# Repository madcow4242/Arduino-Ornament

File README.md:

# Arduino-powered Christmas Ornament (or badge, or anything else)

A custom LED Christmas ornament with advent calendar functionality, built using Arduino and KiCad.  This project can easily be adapted to other formats such as a badge by changing the PCB layout.  

### Key features:
- 30 individually-addressable LEDs
- PWM LED control, with support for up to 12 (or more) simultaneous LEDs
- Fade-in / Fade-out support
- Advent calendar mode included
- User-configurable advent date and brightness settings
- Light level measurement (optional)
- Current measurement via a precision 1-ohm current sense resistor and precision amplified ADC circuit (intended to help optimize power usage prior to software finalization) (optional)
- Optimized to fit within the 4k / 256 byte memory limitations of the ATTiny414, but is also compatible with larger variants such as the ATTiny 814/1614/824/1624/3224
- Production software is configured to run at 8MHz to optimize power usage (instead of default 20MHz) - this can be changed if higher PWM frequency is desired, for example.  (test software still runs at 20MHz)
- \>30 days run time on one set of 3x AAA batteries, using default Production software (5 hours/day on, with auto timer).  Can be run on other 3-5VDC power sources like CR2032 for shorter durations (however, \>3.5V is required for 2.8V LEDs or higher - so stick with ~2.2V LEDs or lower if using 3-3.3V power sources).

## Project Structure

This project is organized into three main directories:

### 1. KiCad Files (`KiCad_PCB_Ornament/`)
Contains all KiCad design files for the PCB:
- Schematic files (.kicad_sch)
- PCB layout files (.kicad_pcb)
- Component libraries (.lib, .dcm)
- Footprint files (.kicad_mod)
- Exported fabrication files (.gbr, .drl) (for the example design / messaging)

The PCB layout can be easily customized with your own text, or into a different physical format or size (like a badge) using KiCad - however if modifying the layout you'll have to re-route the board as well of course.  I chose to put the control electronics on the front of the board (to be geeky), but they could easily be moved to the back to clean up the appearance.

NOTE: the board design includes optional current monitoring circuit and light sensing circuit.  Neither of these are implemented in the production software, however they are fully functional and usable in the test software.  Those features can be ported to production as needed, or removed or unpopulated on the PCB.

### 2. Production Software (`Ornament_production_1/`)
The main firmware for the ornament controller:
- Main Arduino sketch (`Ornament_production_1.ino`)
- Configuration and constants
- LED control algorithms
- Date setting and brightness adjustment routines
- Software fits in under 4k of flash, and uses approx. 70 (of 256) bytes of dynamic storage

### 3. Test/Validation Software (`Ornament_test_1/`)
Code for testing and validating the PCB functionality:
- Calibration routines
- Basic functionality tests
- Hardware verification code
- Software uses less than the ATTiny414's 4k of flash and 256 bytes of dynamic storage
- Includes ADC routines for current monitoring and light level measurement, if needed (not used in production code)

## Production Features

- Advent calendar display (December 1-25)
- Custom LED patterns with twinkling effects, including PWM fade-in, fade-out
- Date setting via button interface
- Adjustable brightness levels (10% to 100%)
- Sleep/wake cycle automation
- Preview mode for manual activation during sleep, without affecting 24-hour auto-on timer

## Hardware Requirements

- Microchip ATtiny414 microcontroller (or others in that series)
- Custom PCB with LED matrix
- Power switch and button for user interface
- Battery or power supply for operation
- Optional serial monitor to view diagnostic output on the UART connections (test software only by default)

## Getting Started

1. Clone this repository
2. Open the KiCad project to view or modify the PCB design
3. Use the Arduino IDE to compile and upload the production firmware to the completed PCB
4. Test with the validation software to verify hardware functionality
5. Modify and install the production software as desired

## License

This project is licensed under the MIT License - see the LICENSE file for details.

## Notes

- Custom LCG (Linear Congruential Generator) for random number generation to save flash space
- Charlieplexing technique for LED control - it uses 6 GPIOs to allow individual addressability for up to 30 LEDs.
- PWM LED control for up to 12 LEDs simultaneously, using 3x 32-step groups for each PWM cycle (4 LEDs per cycle)
- (more LEDs can be controlled simultaneously via configuration, but will limit maximum LED brightness)

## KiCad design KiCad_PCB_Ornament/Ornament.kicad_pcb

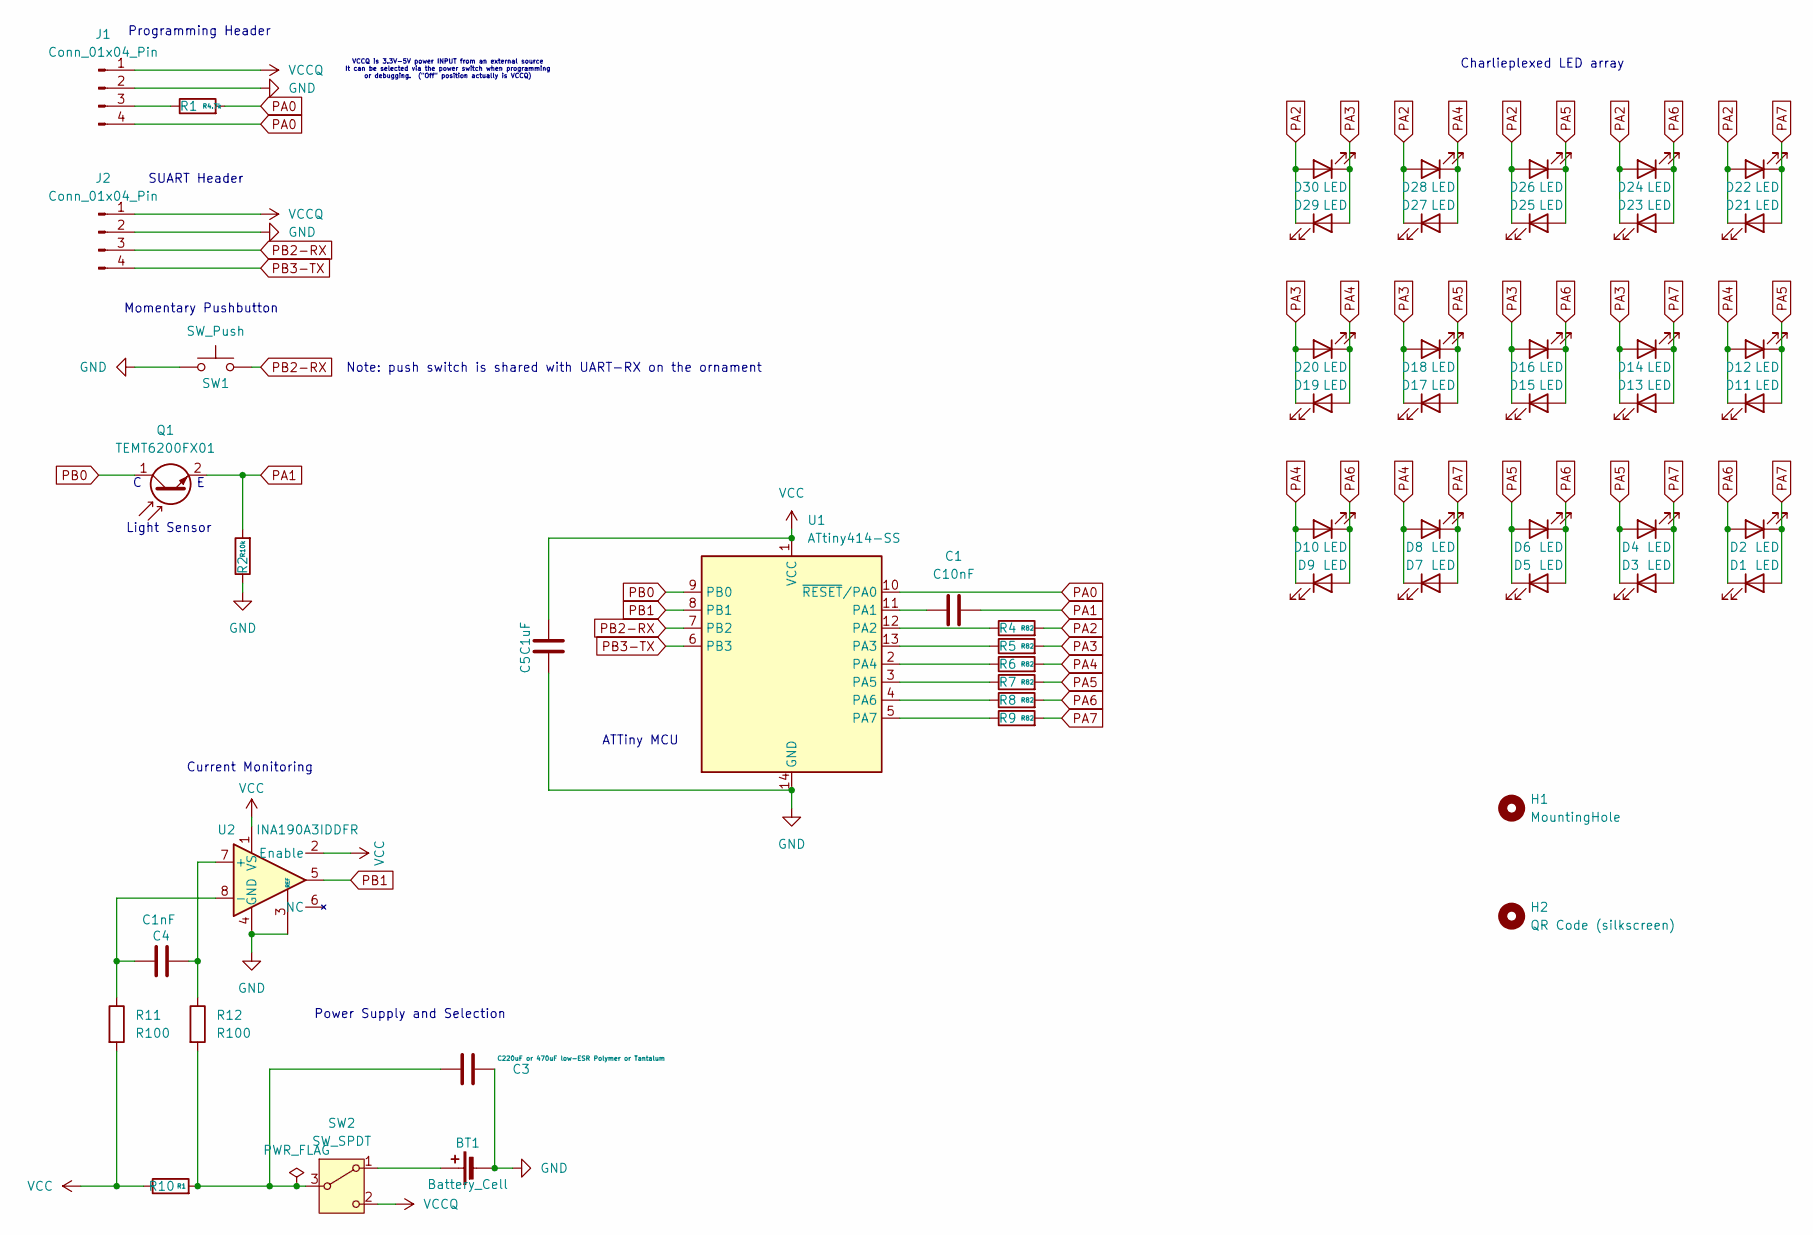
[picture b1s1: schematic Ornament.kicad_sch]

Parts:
BT1: Battery_Cell; BatteryHolder_Keystone_2479_3xAAA-NoHoles
C1: C10nF; C_0603_1608Metric_Pad1.08x0.95mm_HandSolder
C3: C220uF or 470uF low-ESR Polymer or Tantalum; C_1210_3225Metric_Pad1.33x2.70mm_HandSolder
C4: C1nF; C_0603_1608Metric_Pad1.08x0.95mm_HandSolder
C5: C1uF; C_0603_1608Metric_Pad1.08x0.95mm_HandSolder
D1, D2, D3, D4, D5, D6, D7, D8, D9, D10, D11, D12, D13, D14, D15, D16, D17, D18, D19, D20, D21, D22, D23, D24, D25, D26, D27, D28, D29, D30: LED; LED_0603_1608Metric_Pad1.05x0.95mm_HandSolder
H1: MountingHole; MountingHole_2.2mm_M2_DIN965_Pad_TopBottom
H2: QR Code (silkscreen); 15mmQR_cazabon_ornament
J1, J2: Conn_01x04_Pin; PinHeader_1x04_P2.54mm_Vertical
Q1: TEMT6200FX01; R_0805_2012Metric_Pad1.20x1.40mm_HandSolder
R1: R4.7k; R_0603_1608Metric_Pad0.98x0.95mm_HandSolder
R2: R10k; R_0603_1608Metric_Pad0.98x0.95mm_HandSolder
R4, R5, R6, R7, R8, R9: R82; R_0603_1608Metric_Pad0.98x0.95mm_HandSolder
R10: R1; R_1206_3216Metric
R11, R12: R100; R_0603_1608Metric_Pad0.98x0.95mm_HandSolder
SW1: SW_Push; SW_Push_1P1T_NO_E-Switch_TL3301NxxxxxG
SW2: SW_SPDT; CSS1210TB
U1: ATtiny414-SS; SOIC-14_3.9x8.7mm_P1.27mm
U2: INA190A3IDDFR; SOT-23-8_Handsoldering

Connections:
GND: BT1.2 (-), C3.1, C5.1, J1.2, J2.2, R2.1, SW1.1, U1.14 (GND), U2.3 (REF), U2.4 (GND)
unnamed: BT1.1 (+), SW2.1 (A)
unnamed: J1.3, R1.1
unnamed: C3.2, R10.2, R12.2, SW2.3 (B)
unnamed: C1.1, U1.11 (PA1)
unnamed: R4.1, U1.12 (PA2)
unnamed: R5.1, U1.13 (PA3)
unnamed: R6.1, U1.2 (PA4)
unnamed: R7.1, U1.3 (PA5)
unnamed: R8.1, U1.4 (PA6)
unnamed: R9.1, U1.5 (PA7)
unnamed: C4.2, R12.1, U2.7 (+)
unnamed: C4.1, R11.1, U2.8 (-)
PA0: J1.4, R1.2, U1.10 (~RESET/PA0)
PA1: C1.2, Q1.2 (E), R2.2
PA2: D21.1 (K), D22.2 (A), D23.1 (K), D24.2 (A), D25.1 (K), D26.2 (A), D27.1 (K), D28.2 (A), D29.1 (K), D30.2 (A), R4.2
PA3: D13.1 (K), D14.2 (A), D15.1 (K), D16.2 (A), D17.1 (K), D18.2 (A), D19.1 (K), D20.2 (A), D29.2 (A), D30.1 (K), R5.2
PA4: D7.1 (K), D8.2 (A), D9.1 (K), D10.2 (A), D11.1 (K), D12.2 (A), D19.2 (A), D20.1 (K), D27.2 (A), D28.1 (K), R6.2
PA5: D3.1 (K), D4.2 (A), D5.1 (K), D6.2 (A), D11.2 (A), D12.1 (K), D17.2 (A), D18.1 (K), D25.2 (A), D26.1 (K), R7.2
PA6: D1.1 (K), D2.2 (A), D5.2 (A), D6.1 (K), D9.2 (A), D10.1 (K), D15.2 (A), D16.1 (K), D23.2 (A), D24.1 (K), R8.2
PA7: D1.2 (A), D2.1 (K), D3.2 (A), D4.1 (K), D7.2 (A), D8.1 (K), D13.2 (A), D14.1 (K), D21.2 (A), D22.1 (K), R9.2
PB0: Q1.1 (C), U1.9 (PB0)
PB1: U1.8 (PB1), U2.5
PB2-RX: J2.3, SW1.2, U1.7 (PB2)
PB3-TX: J2.4, U1.6 (PB3)
VCC: C5.2, R10.1, R11.2, U1.1 (VCC), U2.1 (VS), U2.2 (Enable)
VCCQ: J1.1, J2.1, SW2.2 (C)

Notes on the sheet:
Programming Header
Current Monitoring
Power Supply and Selection
Light Sensor
VCCQ is 3.3V-5V power INPUT from an external source It can be selected via the power switch when programming or debugging. ("Off" position actually is VCCQ)
Note: push switch is shared with UART-RX on the ornament
ATTiny MCU
Charlieplexed LED array
Momentary Pushbutton
C E
SUART Header

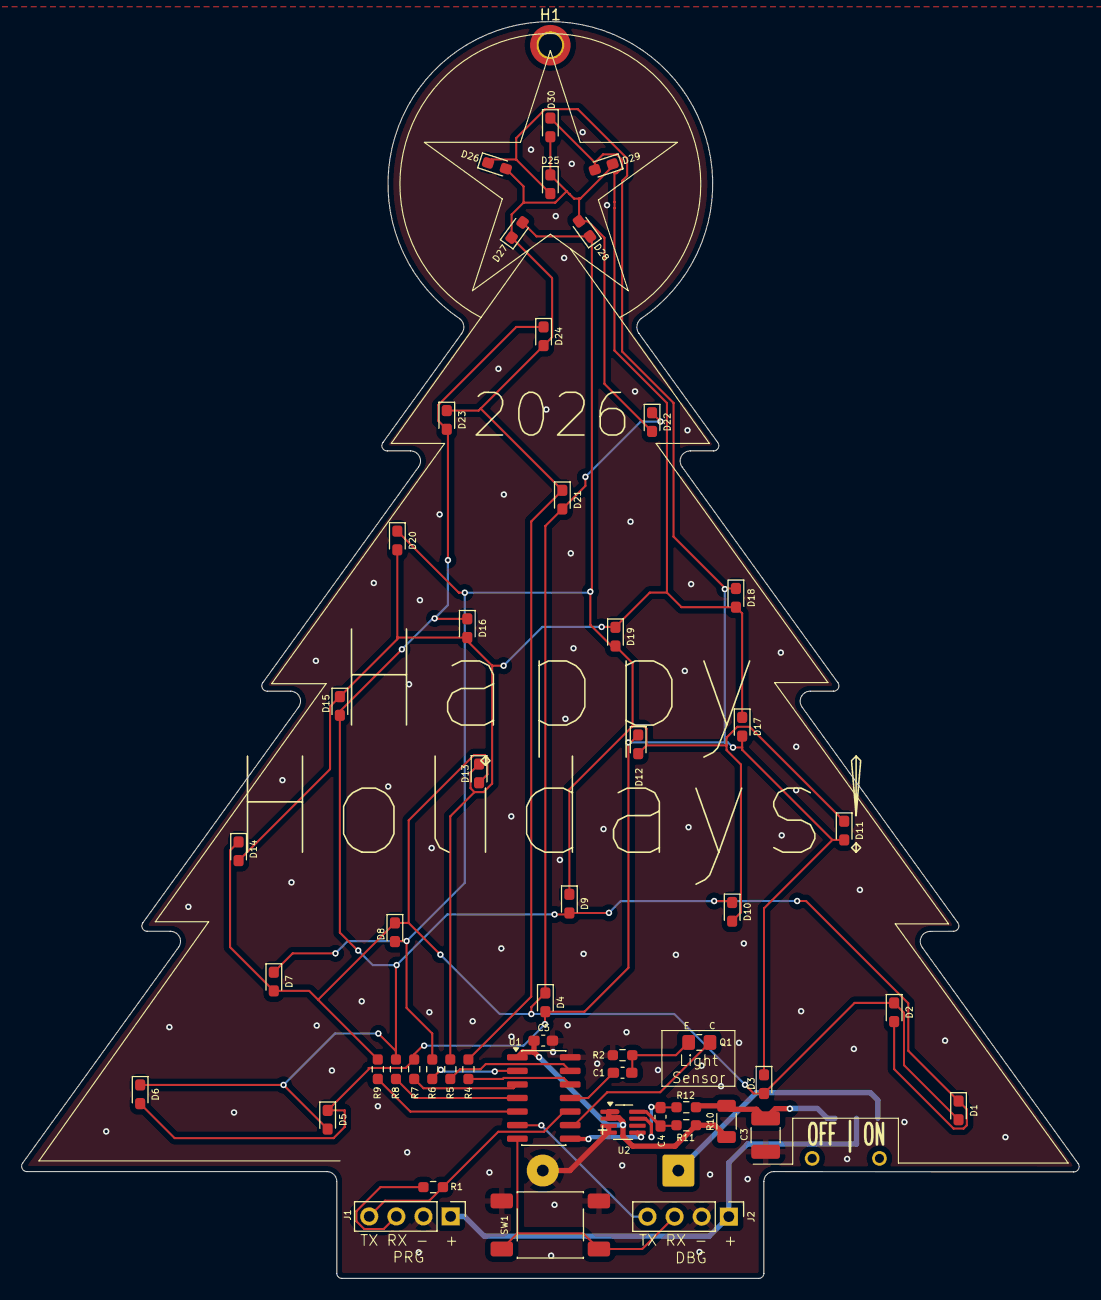
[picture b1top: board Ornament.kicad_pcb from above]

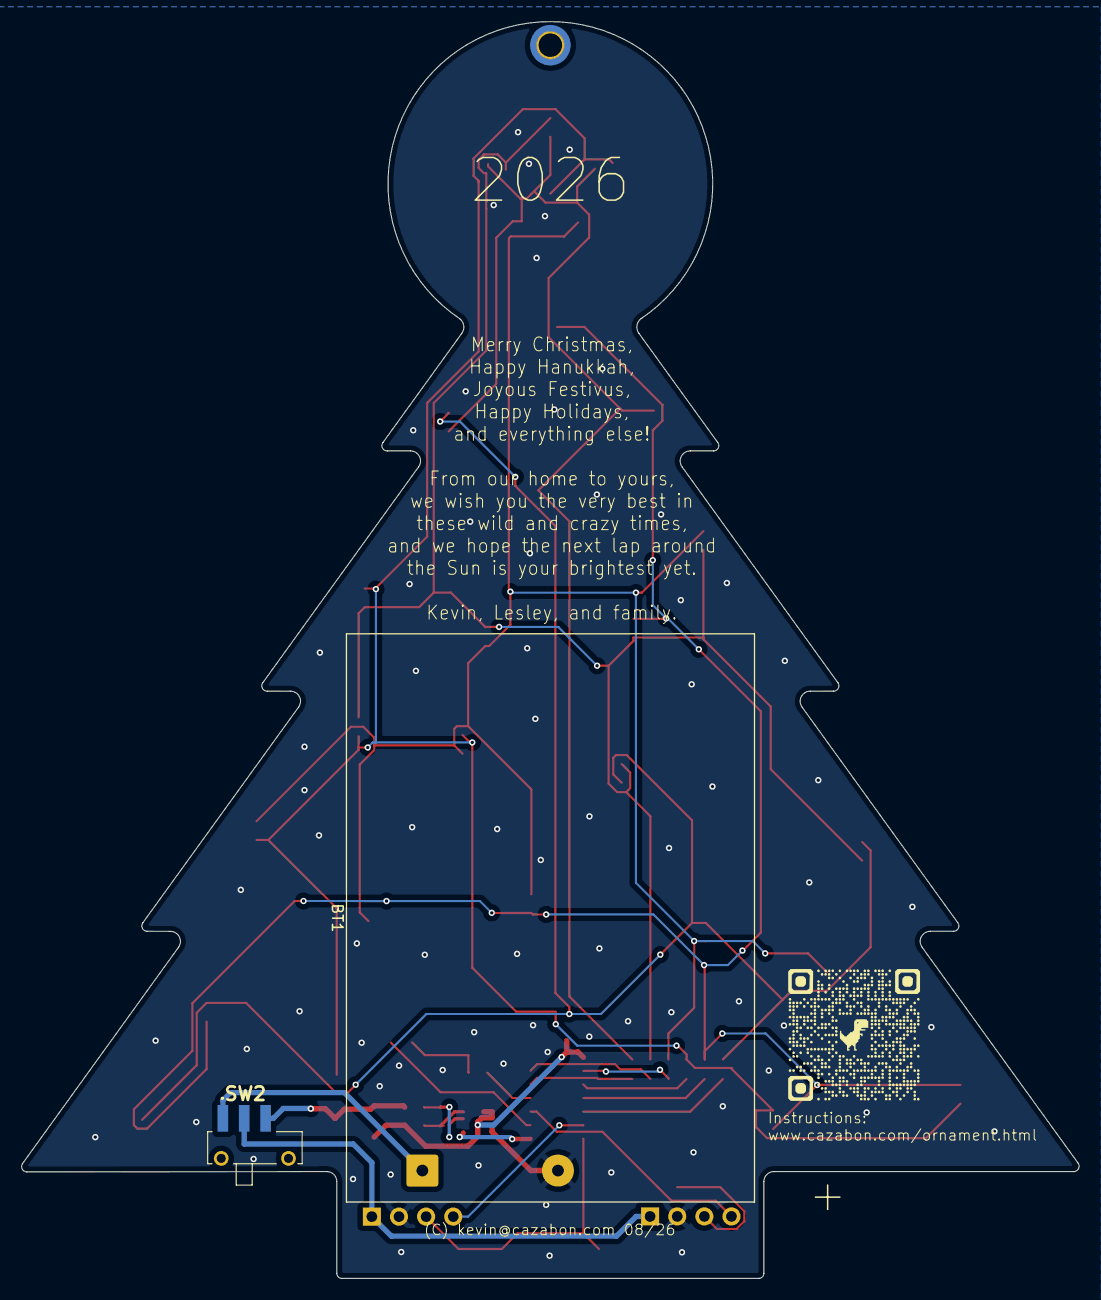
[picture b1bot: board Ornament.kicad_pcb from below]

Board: 2 copper layers, 99.0 x 117.7 mm, 55 parts (3 on the bottom side), 27 nets.
